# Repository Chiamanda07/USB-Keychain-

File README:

# USB - keychain
You might be wondering, why add a USB port to a keychain. Well this keychain inspired and learned from <link sage>  contains an led light that when connected to a usb port lights up.

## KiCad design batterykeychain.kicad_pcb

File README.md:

# Flower Keychain

This is a portable flower keychain PCB with leds, a push button and a coin cell btattery. This project was inspired by [Sage Cadence Light-Up Keychain project](https://sites.google.com/view/sagecadence/home/light-up-keychain).

## Components Used
- 4 LEDs  
- 4 Resistor  
- Push button  
- Mounting hole (for keychain attachment)
- Coin cell
- Coin cell holder

---

## Schematic

---

## PCB Layout

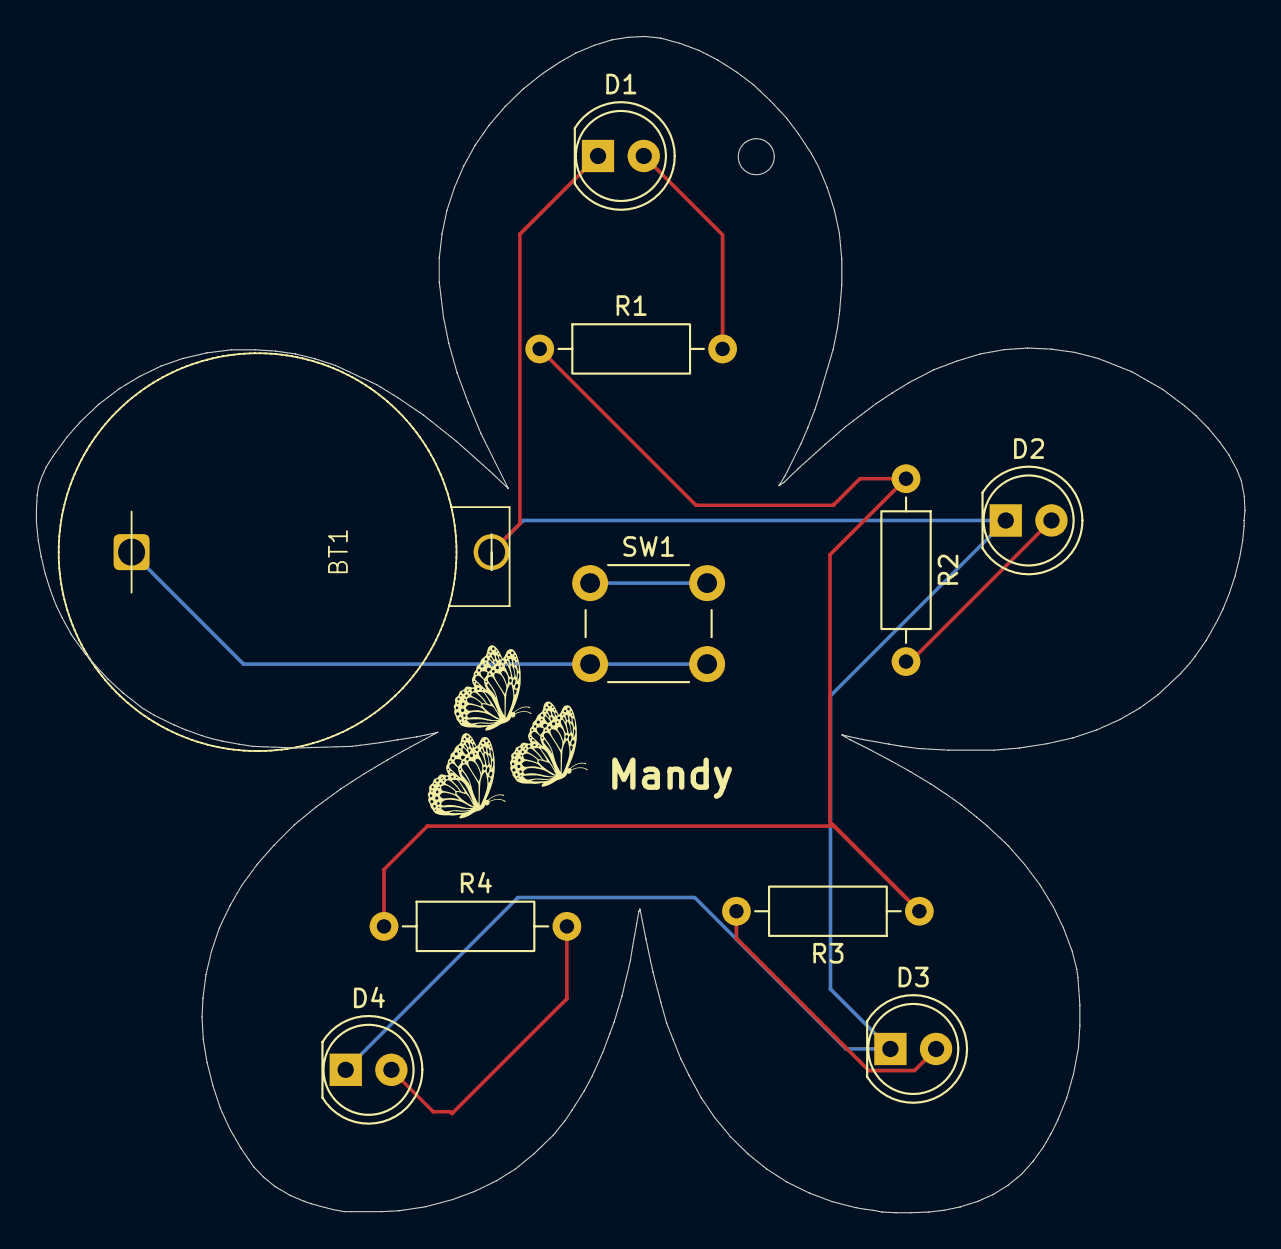
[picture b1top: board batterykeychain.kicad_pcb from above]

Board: 2 copper layers, 67.1 x 65.4 mm, 11 parts (0 on the bottom side), 7 nets.

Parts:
BT1: Battery_Cell; CR2032 Button Battery Holder 2 Pin
D1, D2, D3, D4: LED; LED_D5.0mm
H1: MountingHole; MountingHole_2mm
R1, R2, R3, R4: R; R_Axial_DIN0207_L6.3mm_D2.5mm_P10.16mm_Horizontal
SW1: SW_SPDT; SW_PUSH_6mm

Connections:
unnamed: BT1.1 (+), SW1.2 (B)
unnamed: BT1.2 (-), D1.1 (K), D2.1 (K), D3.1 (K), D4.1 (K)
unnamed: D1.2 (A), R1.2
unnamed: D2.2 (A), R2.2
unnamed: D3.2 (A), R3.2
unnamed: D4.2 (A), R4.2
unnamed: R1.1, R2.1, R3.1, R4.1

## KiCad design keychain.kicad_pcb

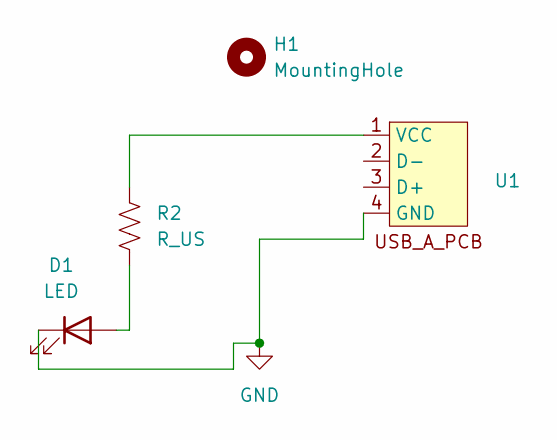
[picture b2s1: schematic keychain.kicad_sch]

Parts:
D1: LED; LED_0402_1005Metric_Pad0.77x0.64mm_HandSolder
H1: MountingHole; MountingHole_2.1mm
R2: R_US; R_0603_1608Metric
U1: USB_A_PCB_sage

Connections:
GND: D1.1 (K), U1.4 (GND)
unnamed: D1.2 (A), R2.2
unnamed: R2.1, U1.1 (VCC)

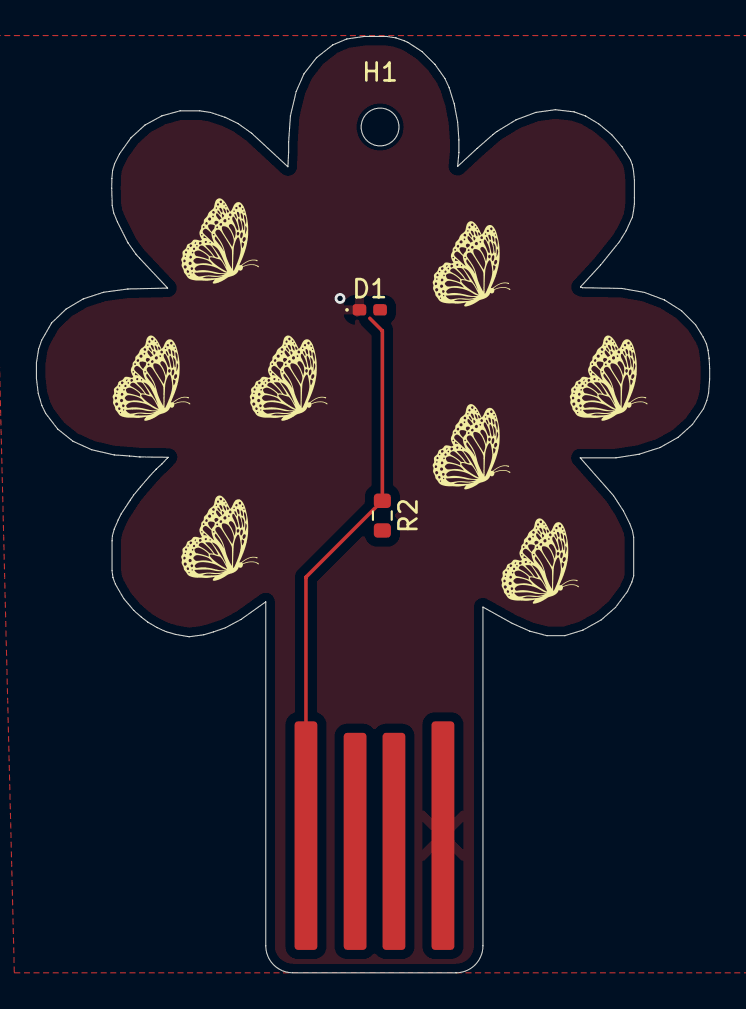
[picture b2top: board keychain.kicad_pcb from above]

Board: 2 copper layers, 37.4 x 52.0 mm, 4 parts (0 on the bottom side), 3 nets.

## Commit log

2026-01-15 Add README for USB keychain project
    Add project description for USB keychain.
2026-01-15 Revise README for USB Keychain project
    Updated README to improve clarity and formatting.
2026-01-15 Add README.md file
2026-01-15 Update README with project inspiration and modifications
    Corrected a repetitive sentence and added details about modifications made to the project.
2026-01-15 Add new file 'hjk' with a newline character
2026-01-15 Rename Screenshot 2026-01-15 144553.png to pcb
2026-01-15 Update PCB image path in README
2026-01-15 Rename Screenshot 2026-01-15 144622.png to schematic
2026-01-15 Revise image links and cleanup PCB section
    Updated image paths and removed file access links for schematic and PCB.
2026-02-03 Rename project to Flower Keychain and update details
    Updated project name and description in README.md. Modified components list to reflect changes.
2026-02-03 Rename Screenshot 2026-02-02 235338.png to pcb
2026-02-03 Rename Screenshot 2026-02-02 235400.png to schematic
2026-02-03 Fix image paths in README for schematic and PCB
2026-02-03 Rename schematic to schematics
2026-02-03 Rename pcb to pcbs
